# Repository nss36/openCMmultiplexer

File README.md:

# openCMmultiplexer
Nicholas Szczecinski 2018
Case Western Reserve University
Cleveland, Ohio, USA

EAGLE and CAM files for an expansion shield for the openCM microcontroller.

You'll also need 5, SOIC 4016D MUX ICs, and pins.

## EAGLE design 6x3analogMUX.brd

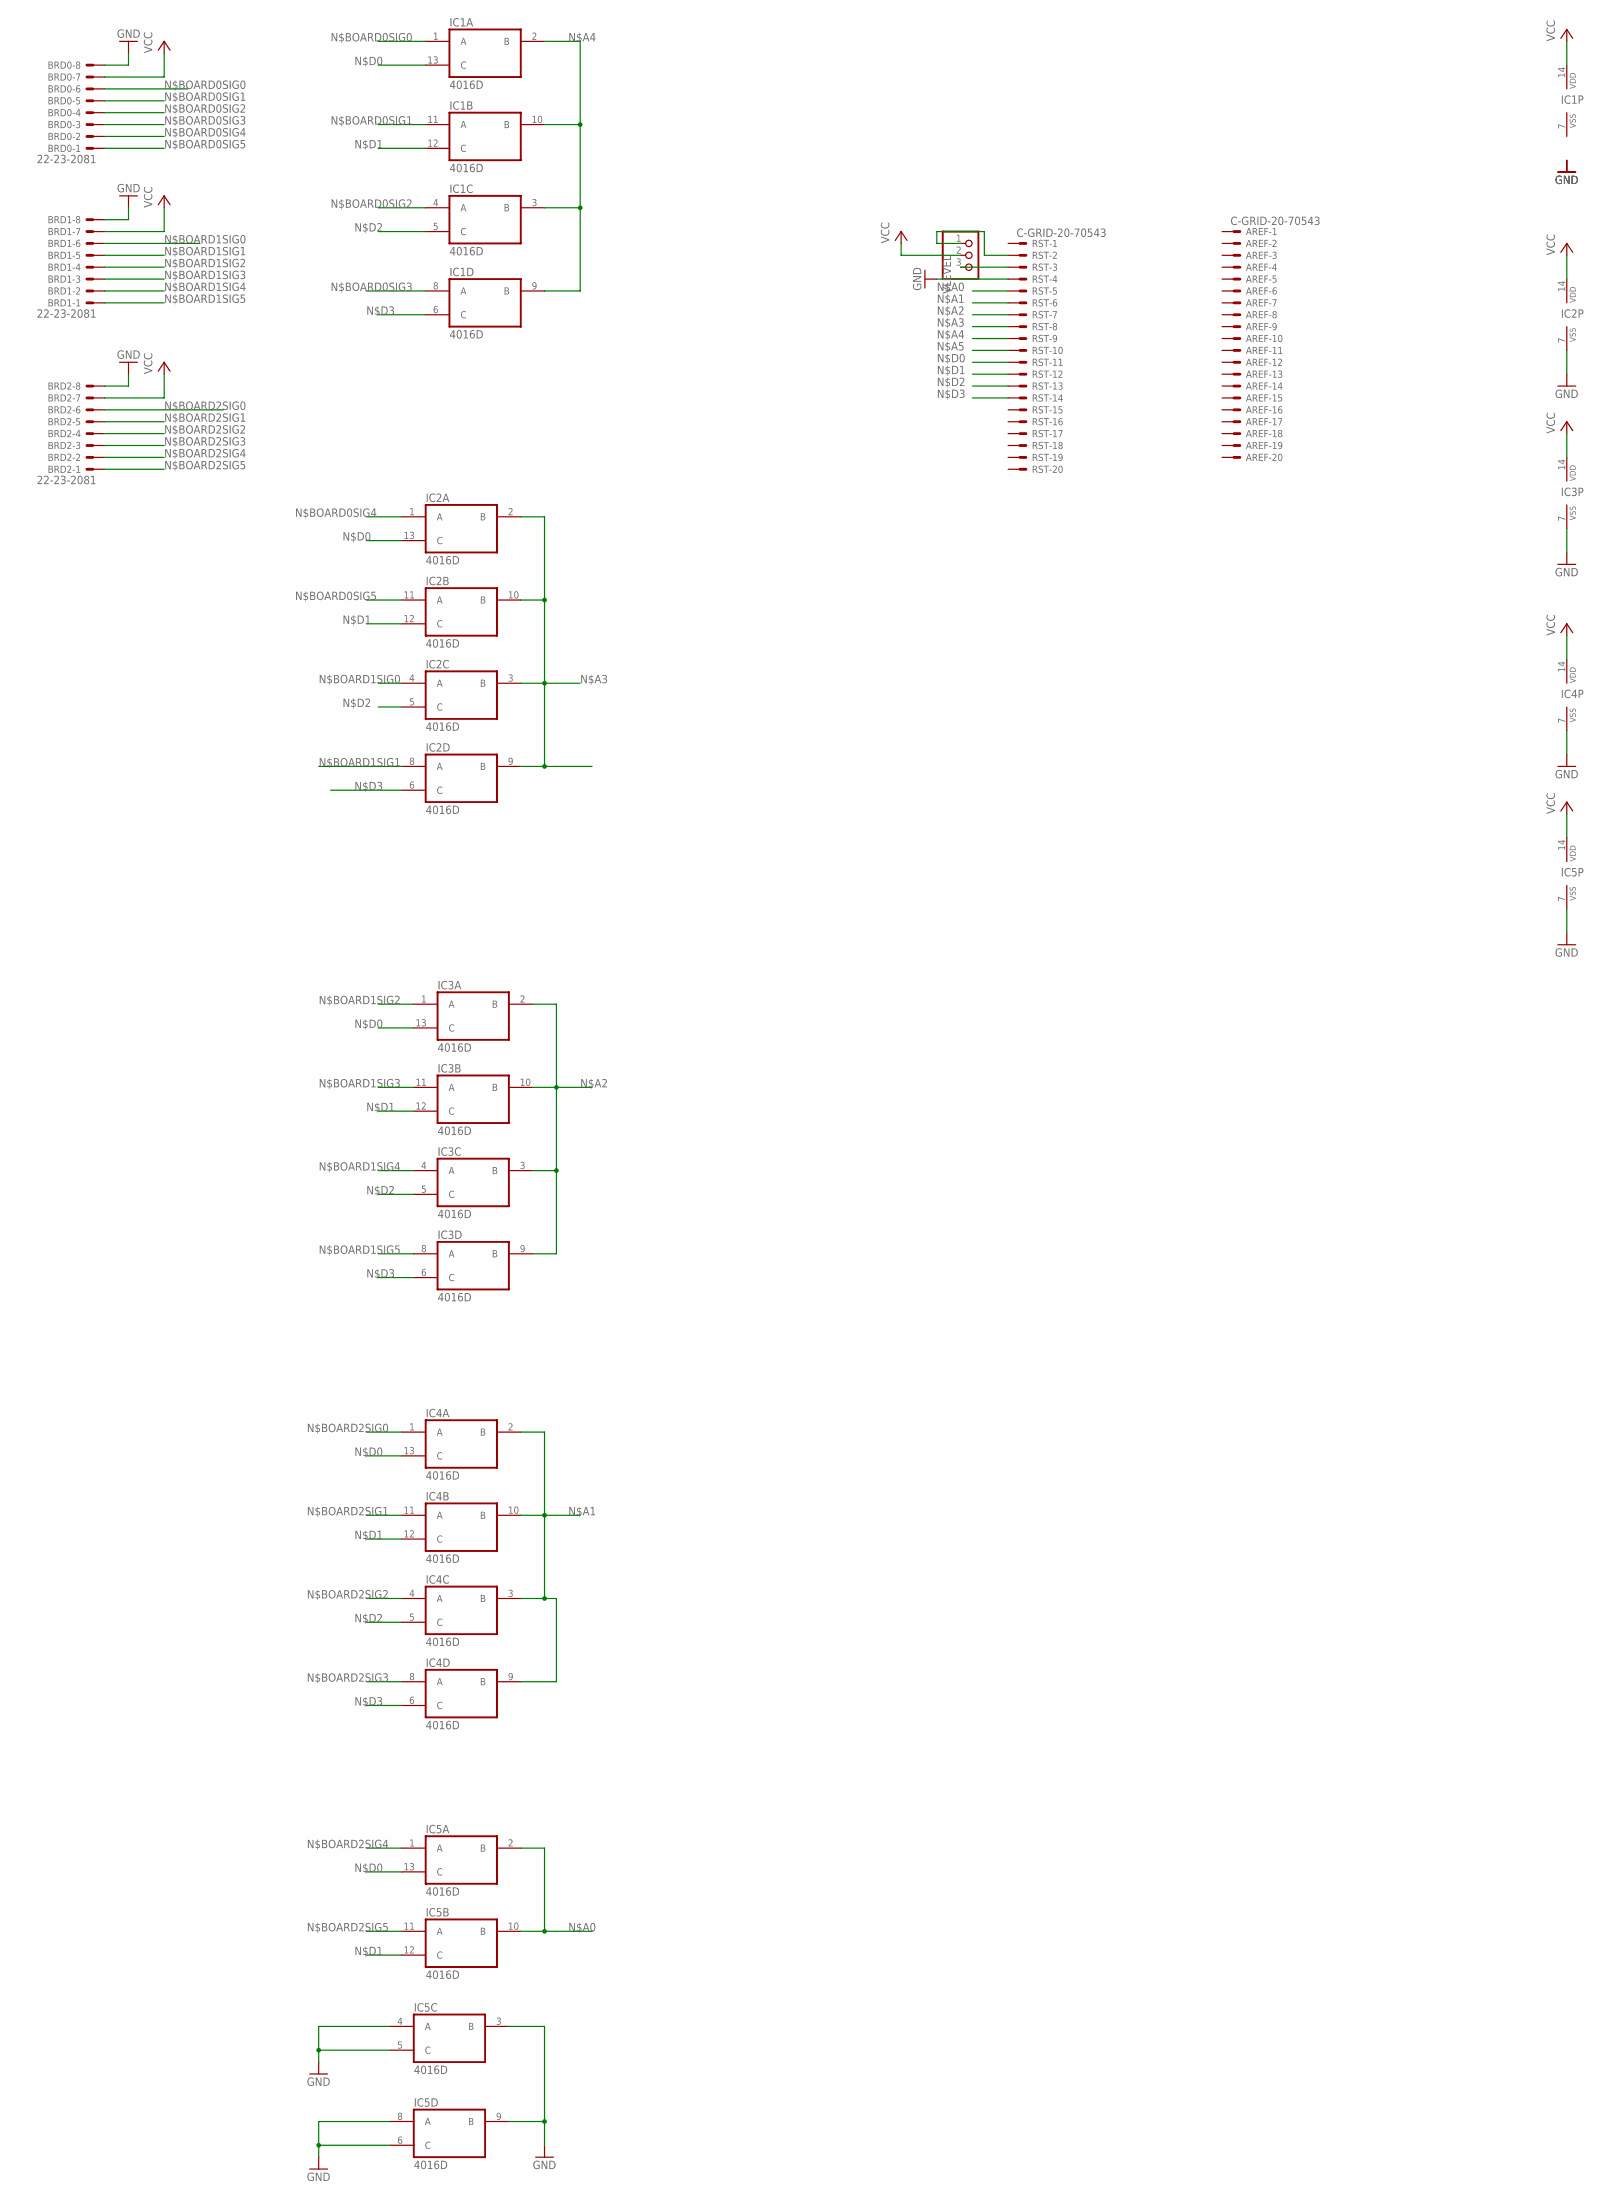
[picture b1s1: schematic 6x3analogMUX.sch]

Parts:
AREF: C-GRID-20-70543; 70543-20
BRD0, BRD1, BRD2: 22-23-2081
IC1, IC2, IC3, IC4, IC5: 4016D; SO14
RST: C-GRID-20-70543; 70543-20
VLEVEL: PINHD-1X3; 1X03

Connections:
GND: BRD0.8, BRD1.8, BRD2.8, IC2.7 (VSS), IC3.7 (VSS), IC4.7 (VSS), IC5.3 (B), IC5.4 (A), IC5.5 (C), IC5.6 (C), IC5.7 (VSS), IC5.8 (A), IC5.9 (B), RST.4
unnamed: RST.3, VLEVEL.3
unnamed: RST.2, VLEVEL.1
N$A0: IC5.2 (B), IC5.10 (B), RST.5
N$A1: IC4.2 (B), IC4.3 (B), IC4.9 (B), IC4.10 (B), RST.6
N$A2: IC3.2 (B), IC3.3 (B), IC3.9 (B), IC3.10 (B), RST.7
N$A3: IC2.2 (B), IC2.3 (B), IC2.9 (B), IC2.10 (B), RST.8
N$A4: IC1.2 (B), IC1.3 (B), IC1.9 (B), IC1.10 (B), RST.9
N$A5: RST.10
N$BOARD0SIG0: BRD0.6, IC1.1 (A)
N$BOARD0SIG1: BRD0.5, IC1.11 (A)
N$BOARD0SIG2: BRD0.4, IC1.4 (A)
N$BOARD0SIG3: BRD0.3, IC1.8 (A)
N$BOARD0SIG4: BRD0.2, IC2.1 (A)
N$BOARD0SIG5: BRD0.1, IC2.11 (A)
N$BOARD1SIG0: BRD1.6, IC2.4 (A)
N$BOARD1SIG1: BRD1.5, IC2.8 (A)
N$BOARD1SIG2: BRD1.4, IC3.1 (A)
N$BOARD1SIG3: BRD1.3, IC3.11 (A)
N$BOARD1SIG4: BRD1.2, IC3.4 (A)
N$BOARD1SIG5: BRD1.1, IC3.8 (A)
N$BOARD2SIG0: BRD2.6, IC4.1 (A)
N$BOARD2SIG1: BRD2.5, IC4.11 (A)
N$BOARD2SIG2: BRD2.4, IC4.4 (A)
N$BOARD2SIG3: BRD2.3, IC4.8 (A)
N$BOARD2SIG4: BRD2.2, IC5.1 (A)
N$BOARD2SIG5: BRD2.1, IC5.11 (A)
N$D0: IC1.13 (C), IC2.13 (C), IC3.13 (C), IC4.13 (C), IC5.13 (C), RST.11
N$D1: IC1.12 (C), IC2.12 (C), IC3.12 (C), IC4.12 (C), IC5.12 (C), RST.12
N$D2: IC1.5 (C), IC2.5 (C), IC3.5 (C), IC4.5 (C), RST.13
N$D3: IC1.6 (C), IC2.6 (C), IC3.6 (C), IC4.6 (C), RST.14
VCC: BRD0.7, BRD1.7, BRD2.7, IC1.14 (VDD), IC2.14 (VDD), IC3.14 (VDD), IC4.14 (VDD), IC5.14 (VDD), VLEVEL.2
VSS: IC1.7 (VSS)

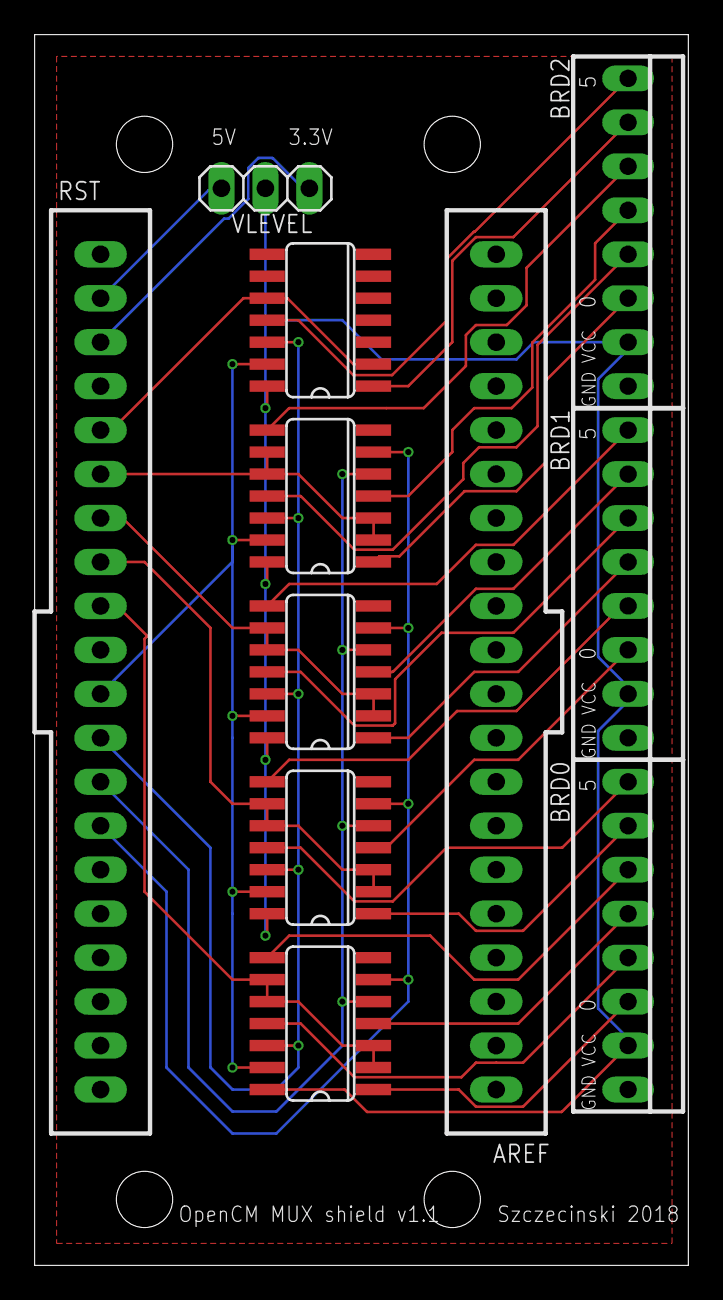
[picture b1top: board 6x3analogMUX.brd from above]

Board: 2 copper layers, 37.8 x 71.1 mm, 11 parts (0 on the bottom side), 31 nets.

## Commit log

2018-12-11 Added files
